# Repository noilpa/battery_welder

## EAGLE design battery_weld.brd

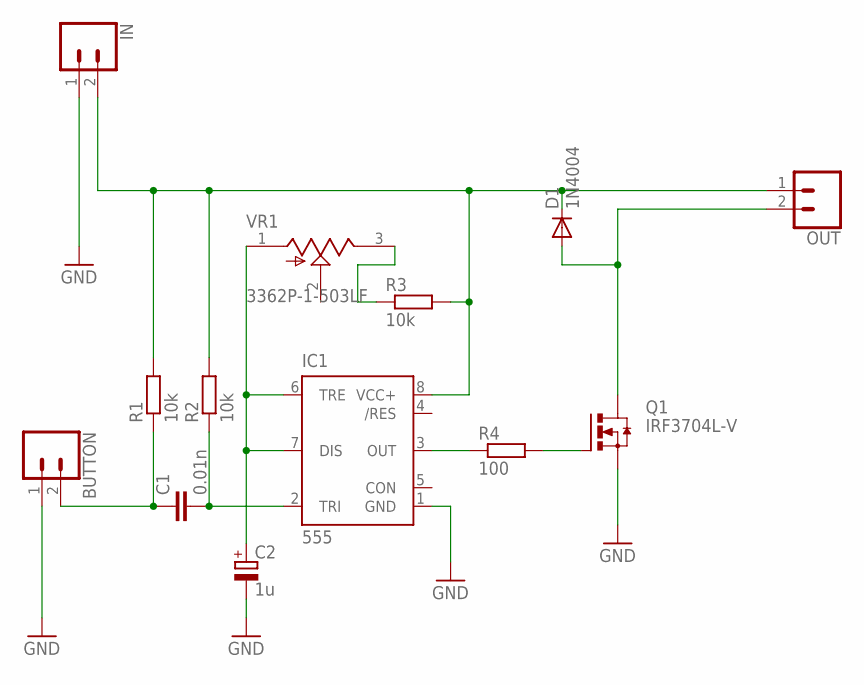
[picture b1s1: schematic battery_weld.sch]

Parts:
BUTTON: CONN_02; 1X02
C1: 0.01n; C1206K
C2: 1u; E2-4
D1: 1N4004; DO41-10
IC1: 555; SO08
IN: CONN_025MM; SCREWTERMINAL-5MM-2
OUT: CONN_025MM; SCREWTERMINAL-5MM-2
Q1: IRF3704L-V; TO262-V
R1, R2, R3: 10k; M1206
R4: 100; M1206
VR1: 3362P-1-503LF; TRIM_3362P-1-503LF

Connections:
GND: BUTTON.1, C2.-, IC1.1 (GND), IN.1, Q1.3 (S)
unnamed: BUTTON.2, C1.1, R1.1
unnamed: C1.2, IC1.2 (TRI), R2.1
unnamed: C2.+, IC1.6 (TRE), IC1.7 (DIS), VR1.1 (CCW)
unnamed: R3.1, VR1.3 (CW)
unnamed: D1.C, IC1.8 (VCC+), IN.2, OUT.1, R1.2, R2.2, R3.2
unnamed: D1.A, OUT.2, Q1.2 (D)
unnamed: Q1.1 (G), R4.2
unnamed: IC1.3 (OUT), R4.1

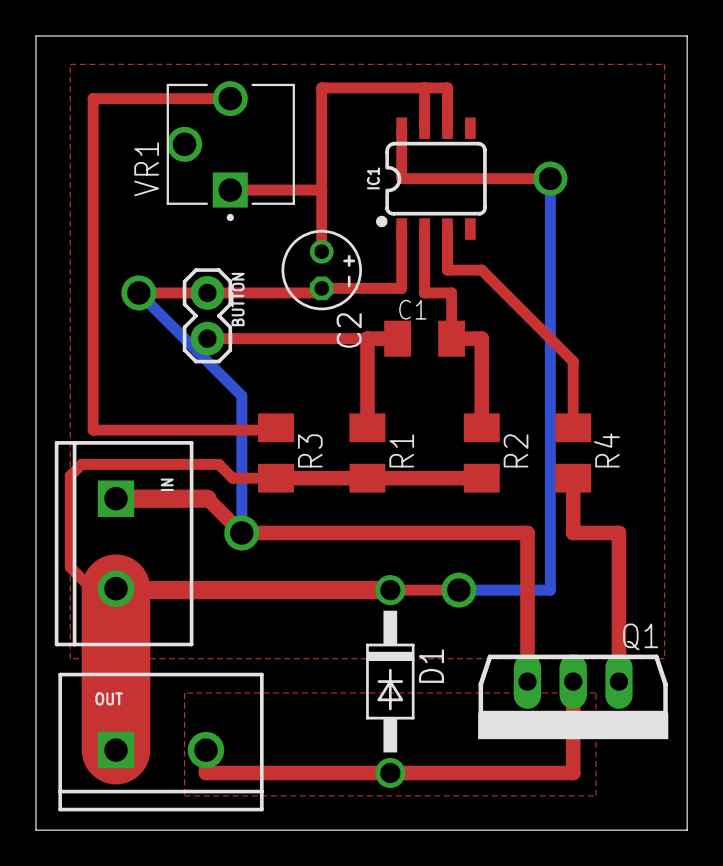
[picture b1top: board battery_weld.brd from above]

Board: 2 copper layers, 36.2 x 44.1 mm, 13 parts (0 on the bottom side), 9 nets.

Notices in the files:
parts and their libraries:
SparkFun-IC-Special-Function: Licensing: Creative Commons ShareAlike 4.0 International - https://creativecommons.org/licenses/by-sa/4.0
